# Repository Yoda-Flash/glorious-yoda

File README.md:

# glorious-yoda
A glorious Yoda PCB with customizable LEDs that change patterns and color based on tilt and movement! Made for Hack Club Fallout's PCB Sprint.

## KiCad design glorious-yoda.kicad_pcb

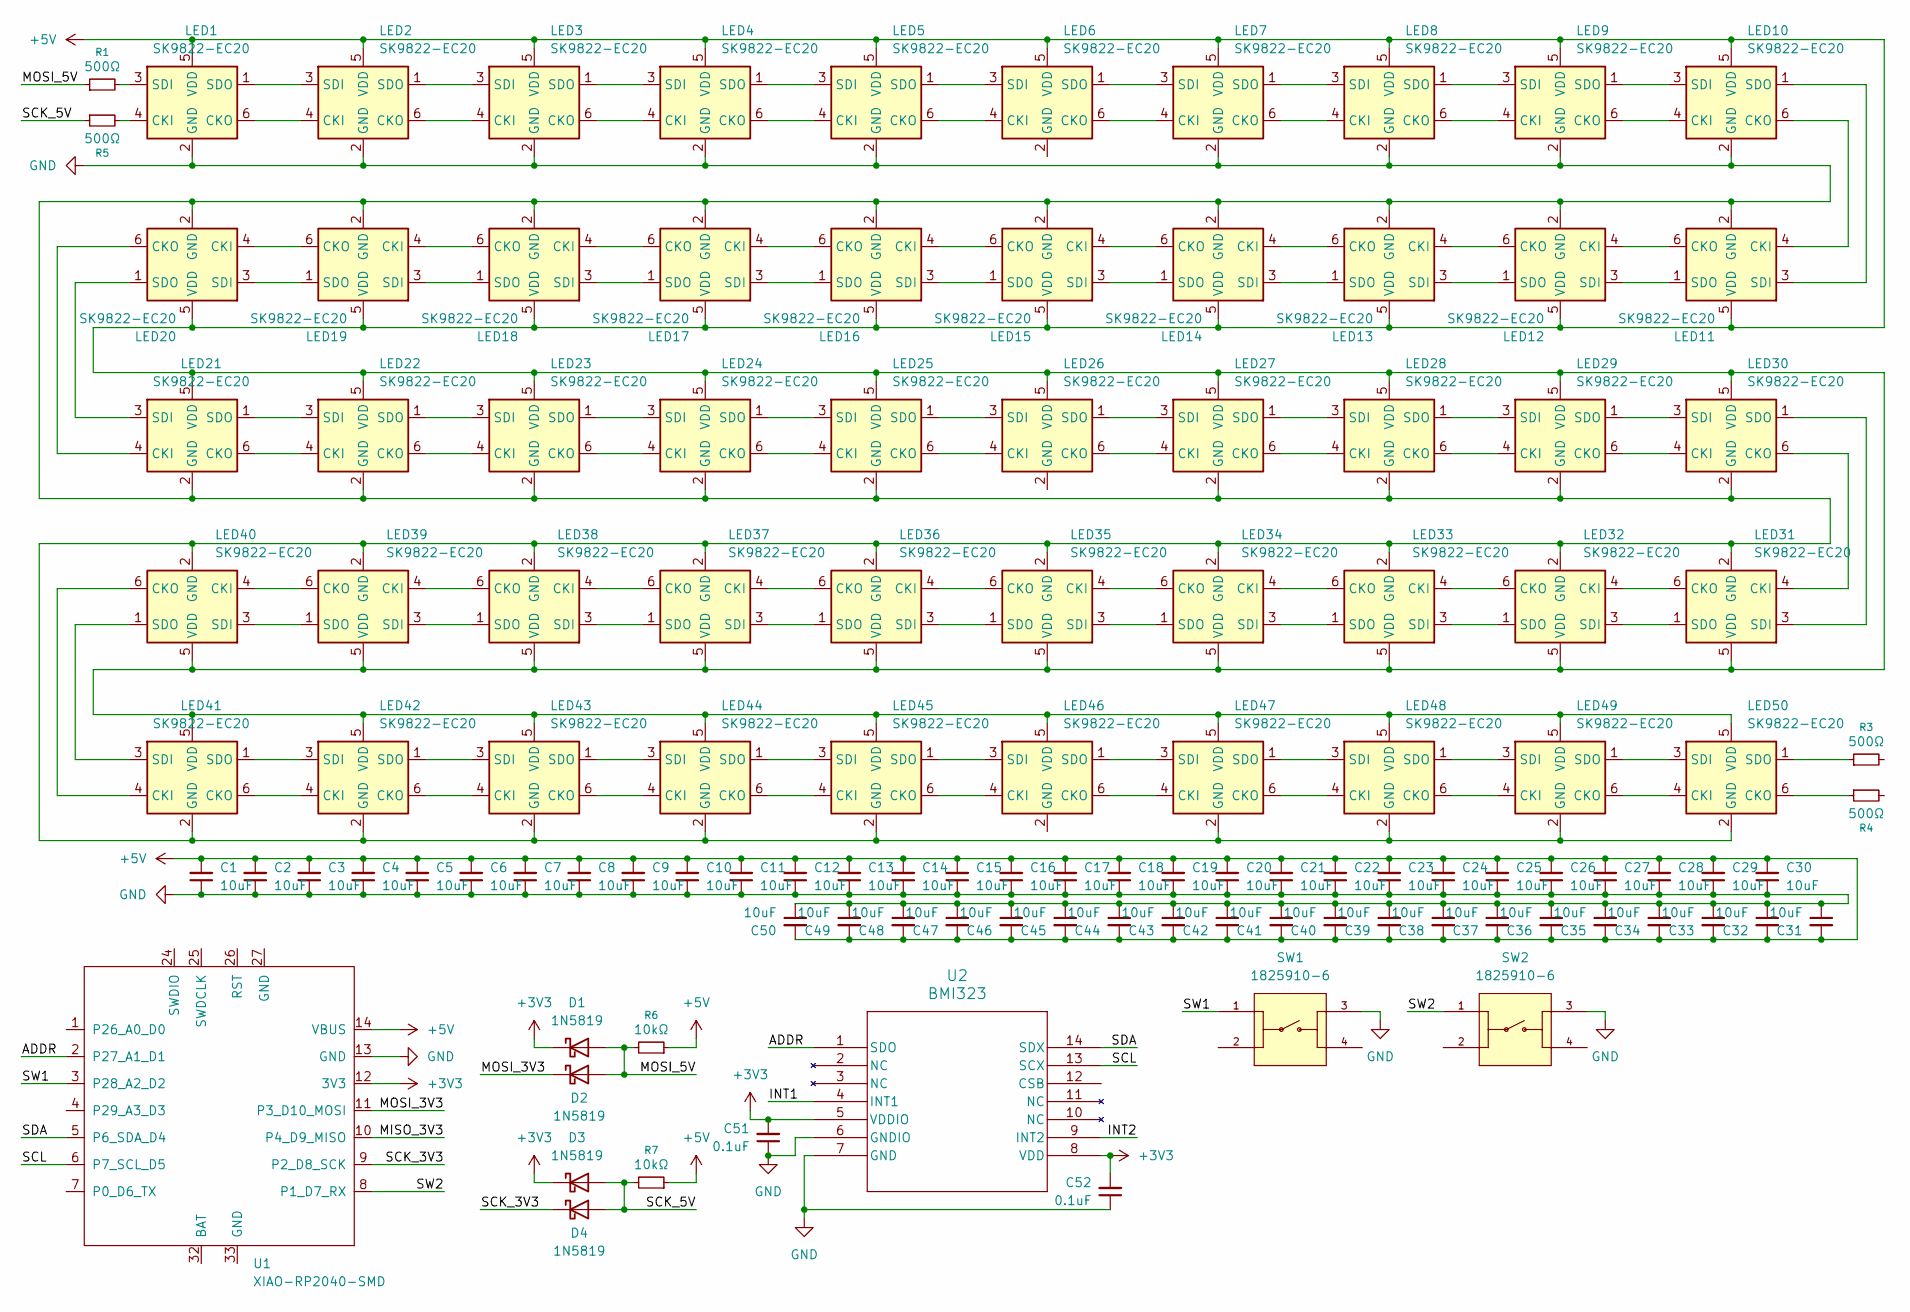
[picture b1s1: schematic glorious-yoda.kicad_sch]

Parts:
C1, C2, C3, C4, C5, C6, C7, C8, C9, C10, C11, C12, C13, C14, C15, C16, C17, C18, C19, C20, C21, C22, C23, C24, C25, C26, C27, C28, C29, C30, C31, C32, C33, C34, C35, C36, C37, C38, C39, C40, C41, C42, C43, C44, C45, C46, C47, C48, C49, C50: 10uF; C_0402_1005Metric
C51, C52: 0.1uF; C_0402_1005Metric
D1, D2, D3, D4: 1N5819; D_SOD-123F
LED1, LED2, LED3, LED4, LED5, LED6, LED7, LED8, LED9, LED10, LED11, LED12, LED13, LED14, LED15, LED16, LED17, LED18, LED19, LED20, LED21, LED22, LED23, LED24, LED25, LED26, LED27, LED28, LED29, LED30, LED31, LED32, LED33, LED34, LED35, LED36, LED37, LED38, LED39, LED40, LED41, LED42, LED43, LED44, LED45, LED46, LED47, LED48, LED49, LED50: SK9822-EC20; SK9822EC20; Manufacturer_Part_Number SK9822-EC20
R1, R3, R4, R5: 500Ω; R_0402_1005Metric
R6, R7: 10kΩ; R_0603_1608Metric
SW1, SW2: 1825910-6; SW_1825910-6-4; PARTREV C10
U1: XIAO-RP2040-SMD
U2: BMI323; BMI323_BOS

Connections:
+3V3: C51.2, C52.2, D1.1 (K), D3.1 (K), U1.12 (3V3), U2.5 (VDDIO), U2.8 (VDD)
+5V: C1.2, C2.2, C3.2, C4.2, C5.2, C6.2, C7.2, C8.2, C9.2, C10.2, C11.2, C12.2, C13.2, C14.2, C15.2, C16.2, C17.2, C18.2, C19.2, C20.2, C21.2, C22.2, C23.2, C24.2, C25.2, C26.2, C27.2, C28.2, C29.2, C30.2, C31.2, C32.2, C33.2, C34.2, C35.2, C36.2, C37.2, C38.2, C39.2, C40.2, C41.2, C42.2, C43.2, C44.2, C45.2, C46.2, C47.2, C48.2, C49.2, C50.2, LED1.5 (VDD), LED2.5 (VDD), LED3.5 (VDD), LED4.5 (VDD), LED5.5 (VDD), LED6.5 (VDD), LED7.5 (VDD), LED8.5 (VDD), LED9.5 (VDD), LED10.5 (VDD), LED11.5 (VDD), LED12.5 (VDD), LED13.5 (VDD), LED14.5 (VDD), LED15.5 (VDD), LED16.5 (VDD), LED17.5 (VDD), LED18.5 (VDD), LED19.5 (VDD), LED20.5 (VDD), LED21.5 (VDD), LED22.5 (VDD), LED23.5 (VDD), LED24.5 (VDD), LED25.5 (VDD), LED26.5 (VDD), LED27.5 (VDD), LED28.5 (VDD), LED29.5 (VDD), LED30.5 (VDD), LED31.5 (VDD), LED32.5 (VDD), LED33.5 (VDD), LED34.5 (VDD), LED35.5 (VDD), LED36.5 (VDD), LED37.5 (VDD), LED38.5 (VDD), LED39.5 (VDD), LED40.5 (VDD), LED41.5 (VDD), LED42.5 (VDD), LED43.5 (VDD), LED44.5 (VDD), LED45.5 (VDD), LED46.5 (VDD), LED47.5 (VDD), LED48.5 (VDD), LED49.5 (VDD), LED50.5 (VDD), R6.1, R7.1, U1.14 (VBUS)
/ADDR: U1.2 (P27_A1_D1), U2.1 (SDO)
/INT1: U2.4 (INT1)
/INT2: U2.9 (INT2)
/MISO_3V3: U1.10 (P4_D9_MISO)
/MOSI_3V3: D2.1 (K), U1.11 (P3_D10_MOSI)
/MOSI_5V: D1.2 (A), D2.2 (A), R1.1, R6.2
/SCK_3V3: D4.1 (K), U1.9 (P2_D8_SCK)
/SCK_5V: D3.2 (A), D4.2 (A), R5.1, R7.2
/SCL: U1.6 (P7_SCL_D5), U2.13 (SCX)
/SDA: U1.5 (P6_SDA_D4), U2.14 (SDX)
/SW1: SW1.1, U1.3 (P28_A2_D2)
/SW2: SW2.1, U1.8 (P1_D7_RX)
GND: C1.1, C2.1, C3.1, C4.1, C5.1, C6.1, C7.1, C8.1, C9.1, C10.1, C11.1, C12.1, C13.1, C14.1, C15.1, C16.1, C17.1, C18.1, C19.1, C20.1, C21.1, C22.1, C23.1, C24.1, C25.1, C26.1, C27.1, C28.1, C29.1, C30.1, C31.1, C32.1, C33.1, C34.1, C35.1, C36.1, C37.1, C38.1, C39.1, C40.1, C41.1, C42.1, C43.1, C44.1, C45.1, C46.1, C47.1, C48.1, C49.1, C50.1, C51.1, C52.1, LED1.2 (GND), LED2.2 (GND), LED3.2 (GND), LED4.2 (GND), LED5.2 (GND), LED7.2 (GND), LED8.2 (GND), LED9.2 (GND), LED10.2 (GND), LED11.2 (GND), LED12.2 (GND), LED13.2 (GND), LED14.2 (GND), LED15.2 (GND), LED16.2 (GND), LED17.2 (GND), LED18.2 (GND), LED19.2 (GND), LED20.2 (GND), LED21.2 (GND), LED22.2 (GND), LED23.2 (GND), LED24.2 (GND), LED25.2 (GND), LED27.2 (GND), LED28.2 (GND), LED29.2 (GND), LED30.2 (GND), LED31.2 (GND), LED32.2 (GND), LED33.2 (GND), LED34.2 (GND), LED35.2 (GND), LED36.2 (GND), LED37.2 (GND), LED38.2 (GND), LED39.2 (GND), LED40.2 (GND), LED41.2 (GND), LED42.2 (GND), LED43.2 (GND), LED44.2 (GND), LED45.2 (GND), LED47.2 (GND), LED48.2 (GND), LED49.2 (GND), LED50.2 (GND), SW1.3, SW2.3, U1.13 (GND), U2.6 (GNDIO), U2.7 (GND)
unnamed: LED1.4 (CKI), R5.2
unnamed: LED1.6 (CKO), LED2.4 (CKI)
unnamed: LED1.3 (SDI), R1.2
unnamed: LED1.1 (SDO), LED2.3 (SDI)
unnamed: LED2.6 (CKO), LED3.4 (CKI)
unnamed: LED2.1 (SDO), LED3.3 (SDI)
unnamed: LED3.6 (CKO), LED4.4 (CKI)
unnamed: LED3.1 (SDO), LED4.3 (SDI)
unnamed: LED4.6 (CKO), LED5.4 (CKI)
unnamed: LED4.1 (SDO), LED5.3 (SDI)
unnamed: LED5.6 (CKO), LED6.4 (CKI)
unnamed: LED5.1 (SDO), LED6.3 (SDI)
unnamed: LED6.6 (CKO), LED7.4 (CKI)
unnamed: LED6.1 (SDO), LED7.3 (SDI)
unnamed: LED7.6 (CKO), LED8.4 (CKI)
unnamed: LED7.1 (SDO), LED8.3 (SDI)
unnamed: LED8.6 (CKO), LED9.4 (CKI)
unnamed: LED8.1 (SDO), LED9.3 (SDI)
unnamed: LED9.6 (CKO), LED10.4 (CKI)
unnamed: LED10.6 (CKO), LED11.4 (CKI)
unnamed: LED9.1 (SDO), LED10.3 (SDI)
unnamed: LED10.1 (SDO), LED11.3 (SDI)
unnamed: LED11.6 (CKO), LED12.4 (CKI)
unnamed: LED11.1 (SDO), LED12.3 (SDI)
unnamed: LED12.6 (CKO), LED13.4 (CKI)
unnamed: LED12.1 (SDO), LED13.3 (SDI)
unnamed: LED13.6 (CKO), LED14.4 (CKI)
unnamed: LED13.1 (SDO), LED14.3 (SDI)
unnamed: LED14.6 (CKO), LED15.4 (CKI)
unnamed: LED14.1 (SDO), LED15.3 (SDI)
unnamed: LED15.6 (CKO), LED16.4 (CKI)
unnamed: LED15.1 (SDO), LED16.3 (SDI)
unnamed: LED16.6 (CKO), LED17.4 (CKI)
unnamed: LED16.1 (SDO), LED17.3 (SDI)
unnamed: LED17.6 (CKO), LED18.4 (CKI)
unnamed: LED17.1 (SDO), LED18.3 (SDI)
unnamed: LED18.6 (CKO), LED19.4 (CKI)
unnamed: LED18.1 (SDO), LED19.3 (SDI)
unnamed: LED19.6 (CKO), LED20.4 (CKI)
unnamed: LED19.1 (SDO), LED20.3 (SDI)
unnamed: LED20.6 (CKO), LED21.4 (CKI)
unnamed: LED20.1 (SDO), LED21.3 (SDI)
unnamed: LED21.6 (CKO), LED22.4 (CKI)
unnamed: LED21.1 (SDO), LED22.3 (SDI)
unnamed: LED22.6 (CKO), LED23.4 (CKI)
unnamed: LED22.1 (SDO), LED23.3 (SDI)
unnamed: LED23.6 (CKO), LED24.4 (CKI)
unnamed: LED23.1 (SDO), LED24.3 (SDI)
unnamed: LED24.6 (CKO), LED25.4 (CKI)
unnamed: LED24.1 (SDO), LED25.3 (SDI)
unnamed: LED25.6 (CKO), LED26.4 (CKI)
unnamed: LED25.1 (SDO), LED26.3 (SDI)
unnamed: LED26.6 (CKO), LED27.4 (CKI)
unnamed: LED26.1 (SDO), LED27.3 (SDI)
unnamed: LED27.6 (CKO), LED28.4 (CKI)
unnamed: LED27.1 (SDO), LED28.3 (SDI)
unnamed: LED28.6 (CKO), LED29.4 (CKI)
unnamed: LED28.1 (SDO), LED29.3 (SDI)
unnamed: LED29.6 (CKO), LED30.4 (CKI)
unnamed: LED29.1 (SDO), LED30.3 (SDI)
unnamed: LED30.6 (CKO), LED31.4 (CKI)
unnamed: LED30.1 (SDO), LED31.3 (SDI)
unnamed: LED31.6 (CKO), LED32.4 (CKI)
unnamed: LED31.1 (SDO), LED32.3 (SDI)
unnamed: LED32.6 (CKO), LED33.4 (CKI)
unnamed: LED32.1 (SDO), LED33.3 (SDI)
unnamed: LED33.6 (CKO), LED34.4 (CKI)
unnamed: LED33.1 (SDO), LED34.3 (SDI)
unnamed: LED34.6 (CKO), LED35.4 (CKI)
unnamed: LED34.1 (SDO), LED35.3 (SDI)
unnamed: LED35.6 (CKO), LED36.4 (CKI)
unnamed: LED35.1 (SDO), LED36.3 (SDI)
unnamed: LED36.6 (CKO), LED37.4 (CKI)
unnamed: LED36.1 (SDO), LED37.3 (SDI)
unnamed: LED37.6 (CKO), LED38.4 (CKI)
unnamed: LED37.1 (SDO), LED38.3 (SDI)
unnamed: LED38.6 (CKO), LED39.4 (CKI)
unnamed: LED38.1 (SDO), LED39.3 (SDI)
unnamed: LED39.6 (CKO), LED40.4 (CKI)
unnamed: LED39.1 (SDO), LED40.3 (SDI)
unnamed: LED40.6 (CKO), LED41.4 (CKI)
unnamed: LED40.1 (SDO), LED41.3 (SDI)
unnamed: LED41.6 (CKO), LED42.4 (CKI)
unnamed: LED41.1 (SDO), LED42.3 (SDI)
unnamed: LED42.6 (CKO), LED43.4 (CKI)
unnamed: LED42.1 (SDO), LED43.3 (SDI)
unnamed: LED43.6 (CKO), LED44.4 (CKI)
unnamed: LED43.1 (SDO), LED44.3 (SDI)
unnamed: LED44.6 (CKO), LED45.4 (CKI)
unnamed: LED44.1 (SDO), LED45.3 (SDI)
unnamed: LED45.6 (CKO), LED46.4 (CKI)
unnamed: LED45.1 (SDO), LED46.3 (SDI)
unnamed: LED46.6 (CKO), LED47.4 (CKI)
unnamed: LED46.1 (SDO), LED47.3 (SDI)
unnamed: LED47.6 (CKO), LED48.4 (CKI)
unnamed: LED47.1 (SDO), LED48.3 (SDI)
unnamed: LED48.6 (CKO), LED49.4 (CKI)
unnamed: LED48.1 (SDO), LED49.3 (SDI)
unnamed: LED49.6 (CKO), LED50.4 (CKI)
unnamed: LED49.1 (SDO), LED50.3 (SDI)
unnamed: LED50.6 (CKO), R4.1
unnamed: LED50.1 (SDO), R3.1

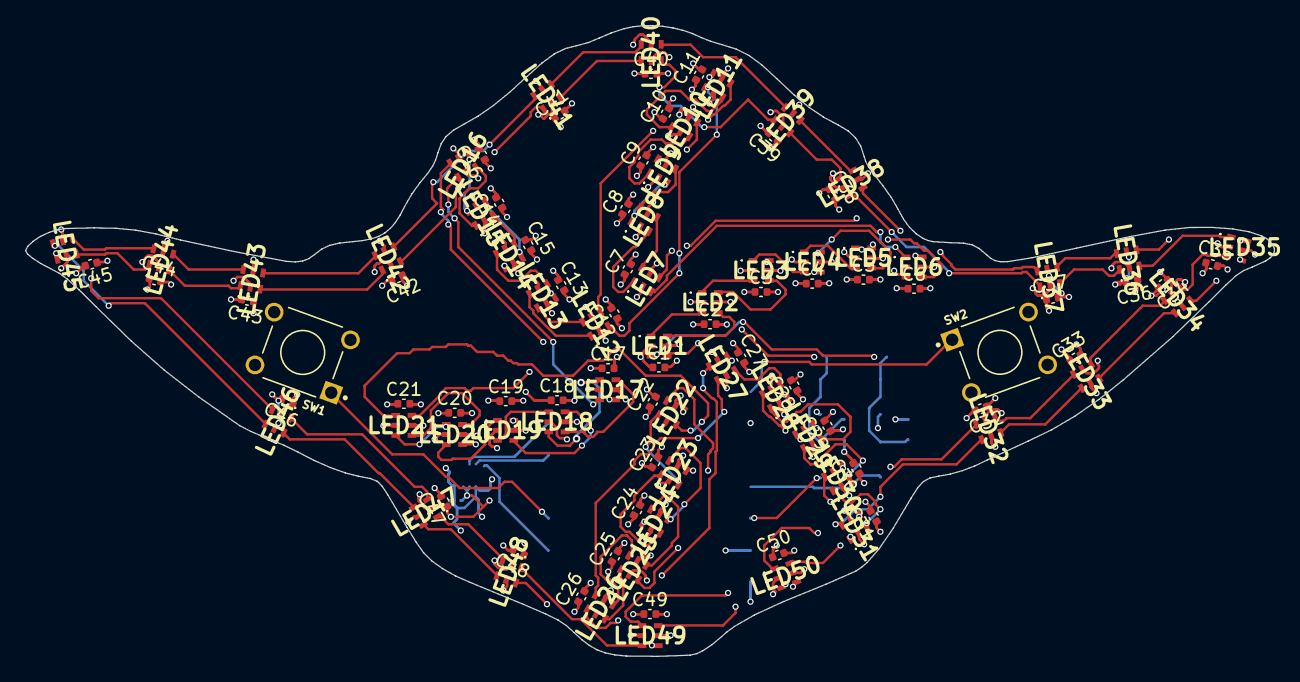
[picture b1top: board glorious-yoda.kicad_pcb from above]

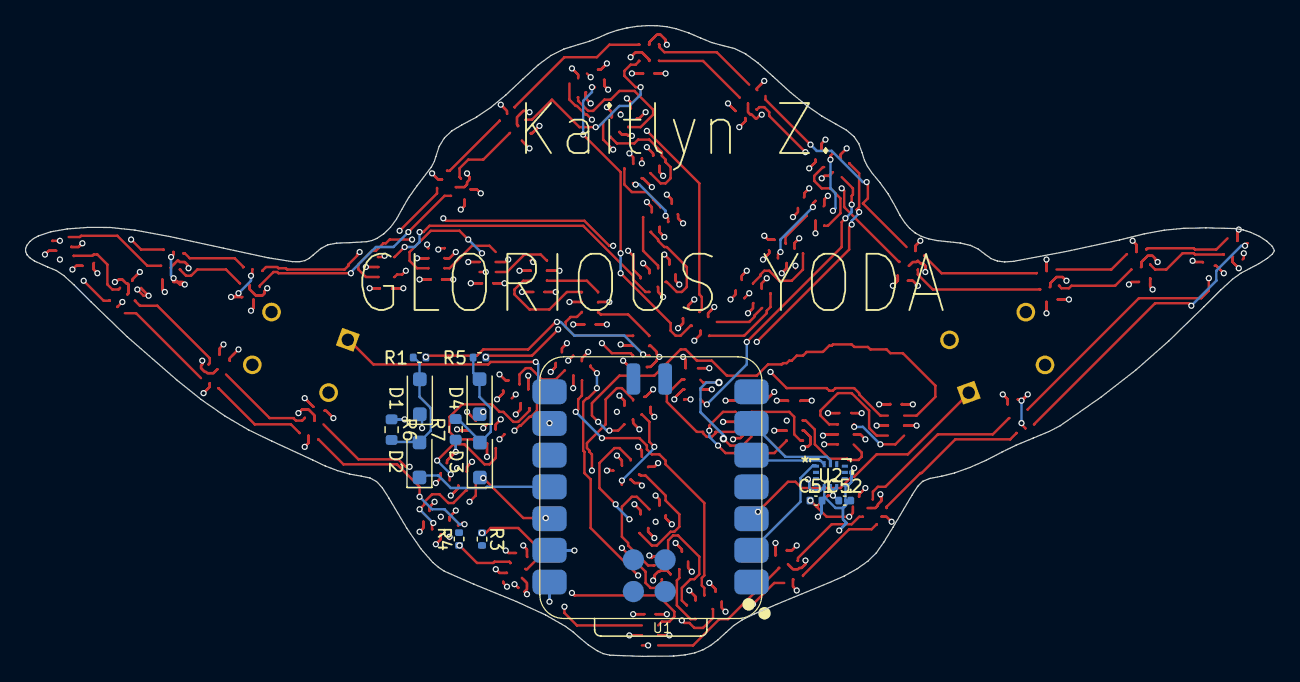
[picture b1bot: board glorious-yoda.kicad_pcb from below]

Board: 4 copper layers, 100.0 x 50.5 mm, 116 parts (14 on the bottom side), 114 nets.
